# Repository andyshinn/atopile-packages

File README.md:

# Andy's atopile Packages

## Packages

* `andyshinn/ebyte-e73`: [nRF52840 ble5.0 SMD 2.4GHz Nordic Wireless Module](https://www.cdebyte.com/products/E73-2G4M08S1C)
* `andyshinn/ebyte-e22`: [E22-900M30S 1W Long Range LoRa Module](https://www.cdebyte.com/products/E22-900M30S)

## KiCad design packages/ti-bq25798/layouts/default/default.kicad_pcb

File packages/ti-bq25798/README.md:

# Texas Instruments BQ25798 Buck-Boost Battery Charger

The BQ25798 is a highly integrated buck-boost charger for 1-4 cell Li-Ion and Li-polymer batteries with dual-input selector and maximum power point tracking (MPPT) for small photovoltaic panels. It supports USB PD 3.0 profile and communicates through I2C interface.

## Features

- 5A buck-boost battery charger with 10mA resolution
- Input voltage range: 3.6V to 24V (absolute maximum 30V)
- Battery voltage range: 2.8V to 18.8V (1-4 cell)
- OTG output voltage: 2.8V to 22V
- I2C controlled (address 0x6B)
- USB PD 3.0 support
- Dual-input power multiplexer (VBUS + VAC1/VAC2)
- Maximum Power Point Tracking (MPPT) for solar panels
- Integrated four switching MOSFETs and BATFET
- 96.5% efficiency at optimal conditions
- Switching frequencies: 750 kHz or 1.5 MHz
- Low quiescent current: 17 µA in battery-only mode
- 500 nA in Charger Shutdown Mode
- 29-pin QFN package (4mm x 4mm)

## Usage

```ato
from "ti-bq25798/bq25798.ato" import BQ25798_driver

module MyCharger:
    charger = new BQ25798_driver

    # Configure charge parameters for your application
    charger.charge_current_limit = 2A +/- 5%      # Custom charge current
    charger.input_current_limit = 1.5A +/- 5%     # Input current limit
    charger.battery_regulation_voltage = 12.6V +/- 1%  # 3S Li-Ion setup

    # Power connections
    usb_input = new ElectricPower
    solar_input = new ElectricPower
    battery_pack = new ElectricPower
    system_rail = new ElectricPower

    # I2C for control
    control_bus = new I2C

    # Connect interfaces
    usb_input ~ charger.power_vbus
    solar_input ~ charger.power_vac1
    battery_pack ~ charger.power_battery
    system_rail ~ charger.power_system
    control_bus ~ charger.i2c

    # External inductor required: connect charger.switch1 and charger.switch2
    # to a 2.2uH, 8A rated inductor (e.g., Bourns SRR1208 series)
```

## Configurable Parameters

- `charge_current_limit`: Maximum charge current (0.1A to 5A, default: 3A)
- `input_current_limit`: Input current limit (0.1A to 3.3A, default: 2A)
- `battery_regulation_voltage`: Battery regulation voltage (2.8V to 18.8V, default: 16.8V for 4S)

## Power Interfaces

- `power_vbus`: USB/adapter input power (3.6V to 24V)
- `power_vac1`: Solar panel or auxiliary input 1 (3.6V to 24V)
- `power_vac2`: Auxiliary input 2 (3.6V to 24V)
- `power_battery`: Battery connection (2.8V to 18.8V, 1-4 cell)
- `power_system`: System output power (2.8V to 22V)
- `power_regn`: Internal 3.3V LDO output
- `power_pmid`: Power path multiplexer output

## Communication

- `i2c`: I2C interface for device control and monitoring (address 0x6B)

## Control Pins

- `charge_enable`: Charge enable control (active low)
- `power_on`: System power on control (active low)
- `input_limit_hiz`: Input current limit / Hi-Z control
- `charge_status`: Charge status output
- `interrupt`: Interrupt output (active low)

## USB Interface

- `usb_dp`: USB D+ data line (for USB PD communication)
- `usb_dm`: USB D- data line (for USB PD communication)

## External Components

- `switch1`, `switch2`: Switching nodes for external inductor connection
- `bootstrap1`, `bootstrap2`: Bootstrap capacitor connections
- `ac_drive1`, `ac_drive2`: AC drive pins
- `source_drive`: Source drive pin

## Additional Features

- `thermal_sense`: Temperature sensing input for thermal regulation
- `program_current`: Programming current setting
- `battery_positive`: Battery positive terminal sensing
- Integrated decoupling capacitors for VBUS, REGN, and SYS rails
- Bootstrap capacitors for switching MOSFETs

## Package Requirements

This package includes the BQ25798RQMR component (29-pin QFN) with symbol, footprint, and 3D model from JLCPCB/LCSC (part number C2876593).

## Contributing

Contributions to this package are welcome via pull requests on the GitHub repository.

## License

This atopile package is provided under the [MIT License](https://opensource.org/license/mit/).

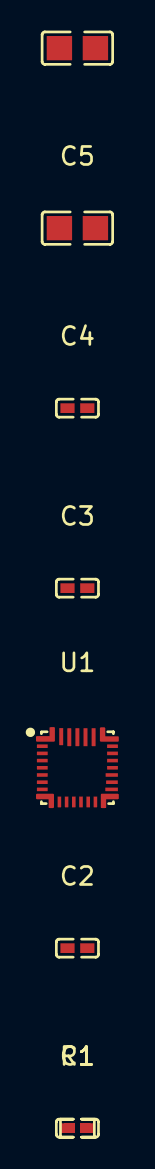
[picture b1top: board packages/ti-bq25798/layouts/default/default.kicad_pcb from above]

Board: 2 copper layers, 8 parts (0 on the bottom side), 10 nets, no tracks yet.

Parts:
C1, C2: 100nF ±20% 25V X5R; C0402
C3: 100nF ±10% 6.3V X7R; C0402
C4: 1µF ±10% 6.3V X5R; C0402
C5: 10µF ±10% 25V X5R; C0805
C6: 10µF ±10% 35V; C0805
R1: 390Ω ±1% 100mW; R0402
U1: QFN-29_L4.0-W4.0-P0.40-TL-BQ25792RQMR

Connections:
GND: C3.2, C4.2, C5.2, C6.2, R1.2, U1.27
PROG: R1.1, U1.20
bootstrap1: C1.1, U1.4
bootstrap2: C2.1, U1.19
power_battery-VCC: U1.22, U1.23
power_regn-VCC: C3.1, C4.1, U1.5
power_system-VCC: C5.1, U1.25
power_vbus-VCC: C6.1, U1.2, U1.3
switch1: C1.2, U1.28
switch2: C2.2, U1.26

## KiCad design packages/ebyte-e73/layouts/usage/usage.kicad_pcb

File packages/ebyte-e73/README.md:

# ebyte_e73_2g4m08s1cx

nRF52840 ble5.0 SMD 2.4GHz Nordic Wireless Module

Created by Andy Shinn <andys@andyshinn.as>

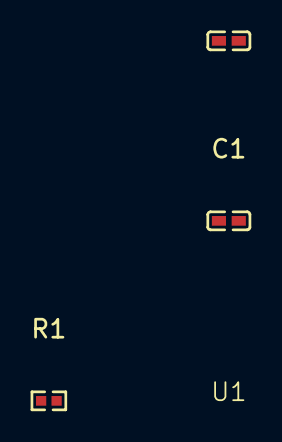
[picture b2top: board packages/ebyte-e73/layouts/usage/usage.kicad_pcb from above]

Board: 2 copper layers, 4 parts (0 on the bottom side), 3 nets, no tracks yet.

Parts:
C1, C2: 100nF ±10% 16V X7R; C0402
R1: 10kΩ ±1% 62.5mW; R0402
U1: E73-2G4M08S1CX

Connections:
GND: C1.2, C2.2, U1.5, U1.21, U1.24
SWD_RESET: R1.2, U1.26
power_vdh-VCC: C1.1, C2.1, R1.1, U1.19, U1.23

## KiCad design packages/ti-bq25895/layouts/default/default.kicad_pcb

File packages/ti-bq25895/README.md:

# Texas Instruments BQ25895 5A Switch-Mode Battery Charger

The BQ25895 is a highly integrated switch-mode battery charge management and system power path management device for single cell Li-Ion and Li-polymer batteries. It supports high input voltage fast chargers and communicates through I2C interface.

## Features

- 5A switch-mode battery charger
- Input voltage range: 3.9V to 14V
- Battery voltage range: 3.0V to 4.5V
- I2C controlled (address 0x6A)
- USB OTG (On-The-Go) boost mode: 4.5V to 5.5V output
- MaxCharge USB detection
- Input current optimization (ICO)
- Power path management with NVDC architecture
- Thermal regulation and protection
- 24-pin WQFN package

## Usage

```ato
from "ti-bq25895/bq25895.ato" import BQ25895_driver

module MyCharger:
    charger = new BQ25895_driver

    # Power connections
    usb_input = new ElectricPower
    battery_pack = new ElectricPower
    system_rail = new ElectricPower

    # I2C for control
    control_bus = new I2C

    # Connect interfaces
    usb_input ~ charger.power_vbus
    battery_pack ~ charger.power_battery
    system_rail ~ charger.power_system
    control_bus ~ charger.i2c
```

## Power Interfaces

- `power_vbus`: USB/adapter input power (3.9V to 14V)
- `power_battery`: Battery connection (3.0V to 4.5V)
- `power_system`: System output power (3.5V to 14V)
- `power_regn`: Internal 3.3V LDO output

## Communication

- `i2c`: I2C interface for device control and monitoring (address 0x6A)

## Control Pins

- `charge_enable`: Charge enable control
- `otg_enable`: OTG boost mode enable
- `input_select`: Input current limit selection
- `charge_status`: Charge status output
- `interrupt`: Interrupt output
- `power_on`: System power on control

## USB Interface

- `usb_dp`: USB D+ data line
- `usb_dm`: USB D- data line

## Additional Features

- `thermal_sense`: Temperature sensing input
- `current_limit`: Input current limit setting
- Integrated decoupling capacitors for VBUS and REGN rails

## Package Requirements

This package requires you to create the BQ25895 component part, symbol, and footprint. The component uses a 24-pin WQFN package.

## Contributing

Contributions to this package are welcome via pull requests on the GitHub repository.

## License

This atopile package is provided under the [MIT License](https://opensource.org/license/mit/).

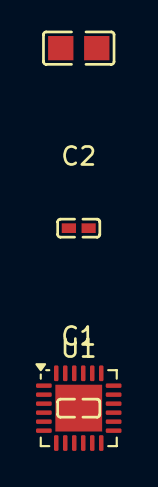
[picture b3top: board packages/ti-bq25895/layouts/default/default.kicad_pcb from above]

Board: 2 copper layers, 4 parts (0 on the bottom side), 3 nets, no tracks yet.

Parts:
C1: 100nF ±10% 6.3V X7R; C0402
C2: 1µF ±10% 6.3V X5R; C0402
C3: 10µF ±10% 25V X5R; C0805
U1: WQFN-24-1EP_4x4mm_P0.5mm_EP2.6x2.6mm

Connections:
GND: C1.2, C2.2, C3.2, U1.10, U1.19
power_regn-VCC: C1.1, C2.1, U1.2
power_vbus-VCC: C3.1, U1.5

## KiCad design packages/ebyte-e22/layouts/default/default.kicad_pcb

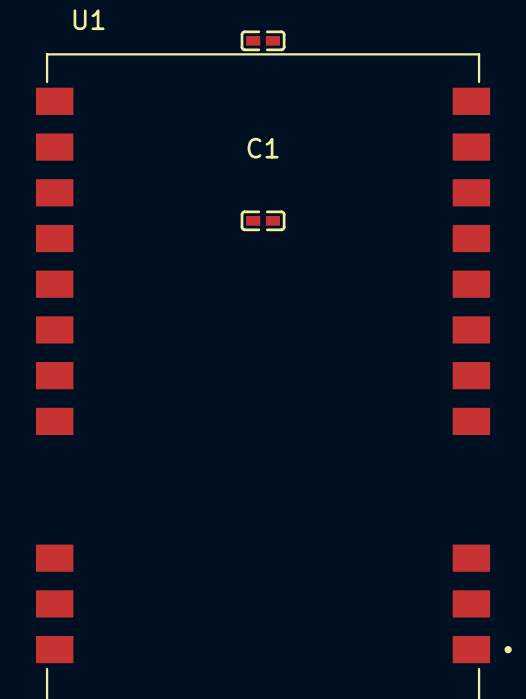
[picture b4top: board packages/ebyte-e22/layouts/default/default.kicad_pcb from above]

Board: 2 copper layers, 3 parts (0 on the bottom side), 2 nets, no tracks yet.

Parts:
C1, C2: 100nF ±10% 16V X7R; C0402
U1: E22-900M30S

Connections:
GND: C1.2, C2.2, U1.1, U1.2, U1.3, U1.4, U1.5, U1.11, U1.12, U1.20, U1.22
VCC: C1.1, C2.1, U1.9, U1.10

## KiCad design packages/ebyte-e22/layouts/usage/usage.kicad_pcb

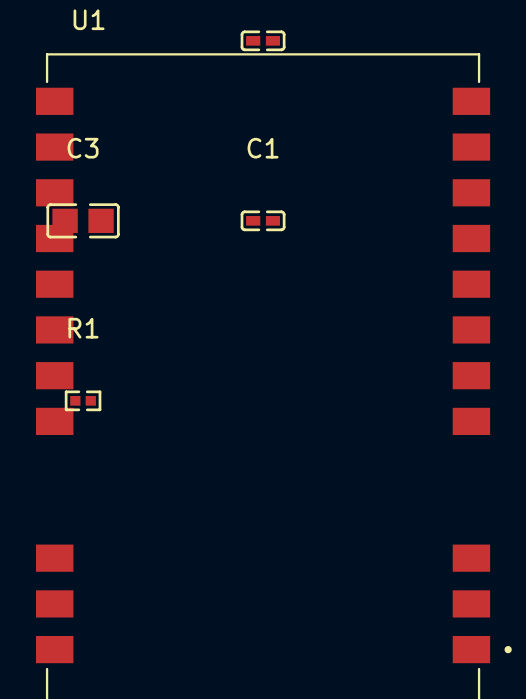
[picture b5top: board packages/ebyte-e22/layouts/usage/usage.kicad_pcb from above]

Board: 2 copper layers, 5 parts (0 on the bottom side), 3 nets, no tracks yet.

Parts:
C1, C2: 100nF ±10% 16V X7R; C0402
C3: 10µF ±10% 25V X5R; C0805
R1: 10kΩ ±1% 62.5mW; R0402
U1: E22-900M30S

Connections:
GND: C1.2, C2.2, C3.2, U1.1, U1.2, U1.3, U1.4, U1.5, U1.11, U1.12, U1.20, U1.22
VCC: C1.1, C2.1, C3.1, R1.1, U1.9, U1.10
reset-line: R1.2, U1.15

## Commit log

2025-09-27 initial
2025-09-27 compile E22
2025-09-28 BQ25895
2025-09-28 adding has_part_picked trait to all
2025-09-29 JST-PH 2pin
2025-09-29 INA3221
2025-09-29 BQ25798
